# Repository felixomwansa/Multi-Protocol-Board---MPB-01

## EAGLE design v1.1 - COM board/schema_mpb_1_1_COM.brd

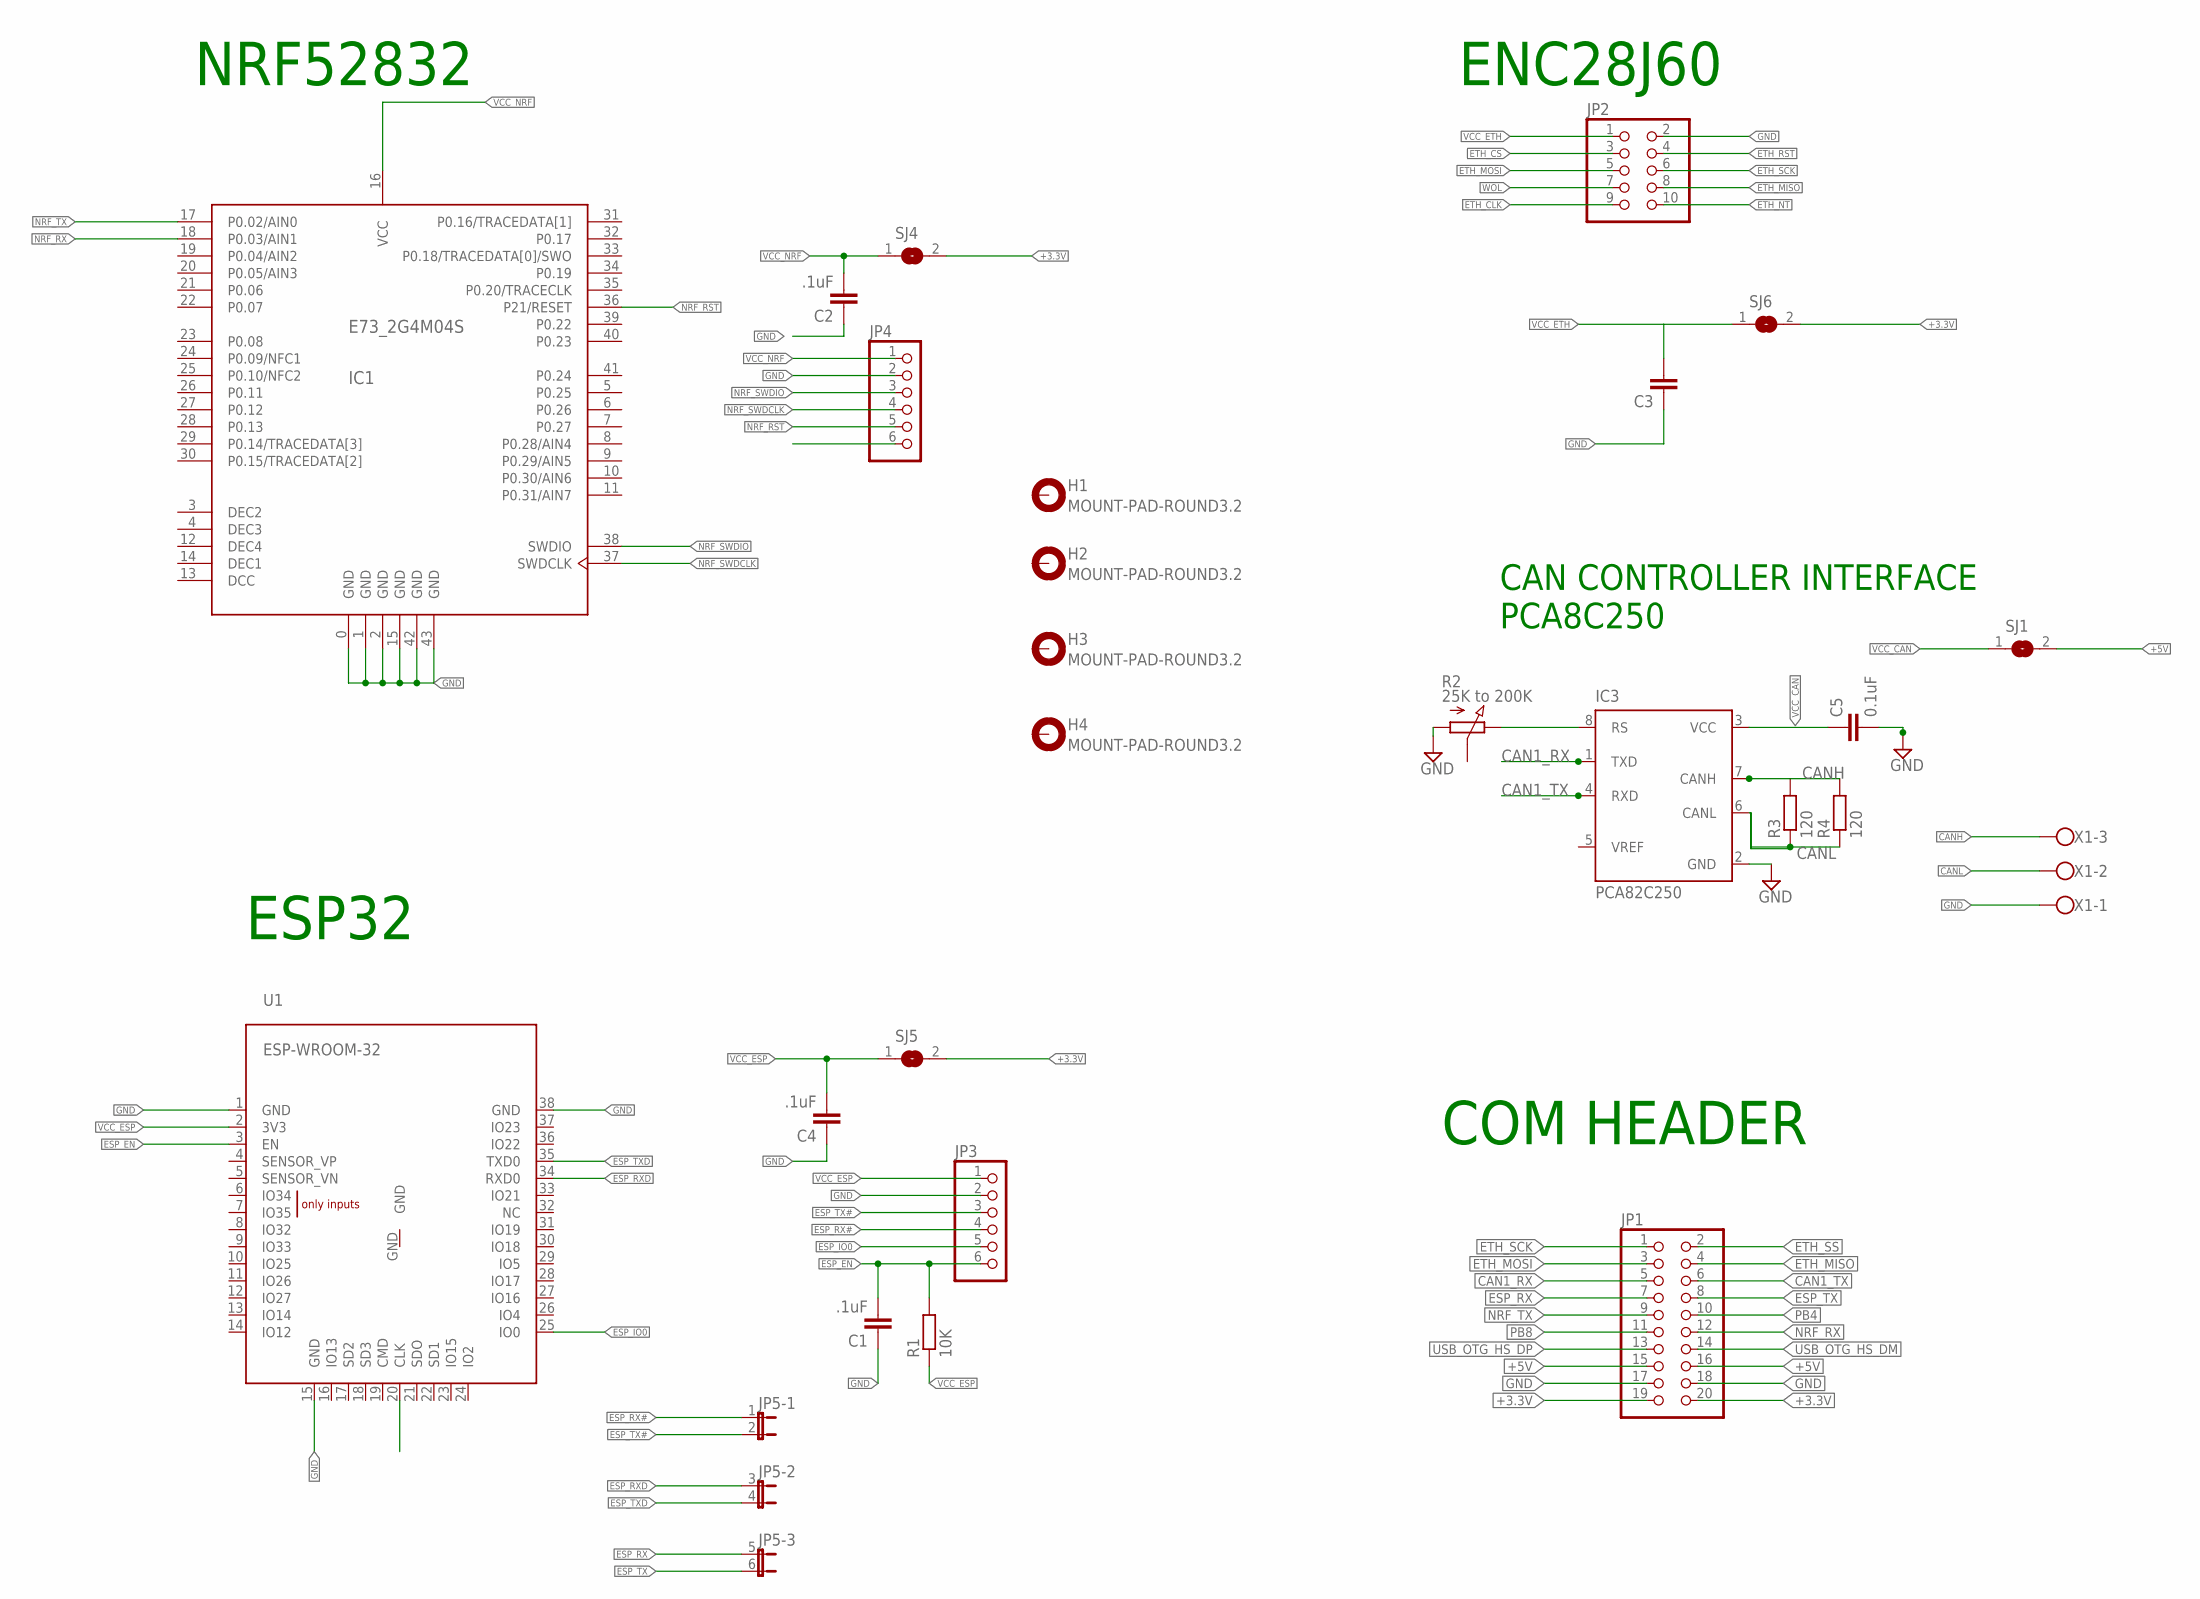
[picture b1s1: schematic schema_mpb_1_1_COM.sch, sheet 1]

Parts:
C1, C2, C4: .1uF; C0603
C3: C-EUC0603; C0603
C5: 0.1uF; C0805
H1, H2, H3, H4: MOUNT-PAD-ROUND3.2; 3,2-PAD
IC1: E73_2G4M04S
IC3: PCA82C250; DIL08
JP1: PINHD-2X10; 2X10
JP2: PINHD-2X5; 2X05
JP3, JP4: PINHD-1X6; 1X06
JP5: JP3QE; JP3Q
R1: 10K; R0603
R2: 25K to 200K; PC25
R3, R4: 120; R0805
SJ1, SJ4, SJ5, SJ6: SJW
U1: ESP-WROOM-32
X1: W237-103

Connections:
+3.3V: JP1.19, JP1.20, SJ4.2, SJ5.2, SJ6.2
+5V: JP1.15, JP1.16, SJ1.2
CAN1_RX: IC3.1 (TXD), JP1.5
CAN1_TX: IC3.4 (RXD), JP1.6
CANH: IC3.7 (CANH), R3.2, R4.2, X1.3
CANL: IC3.6 (CANL), R3.1, R4.1, X1.2
DCC: IC1.13 (DCC)
DEC1: IC1.14 (DEC1)
DEC2: IC1.3 (DEC2)
DEC3: IC1.4 (DEC3)
DEC4: IC1.12 (DEC4)
ESP_EN: C1.2, JP3.6, R1.2, U1.3 (EN)
ESP_IO0: JP3.5, U1.25 (IO0)
ESP_RX: JP1.7, JP5.5 (1)
ESP_RX#: JP3.4, JP5.1
ESP_RXD: JP5.3 (1), U1.34 (RXD0)
ESP_TX: JP1.8, JP5.6 (2)
ESP_TX#: JP3.3, JP5.2
ESP_TXD: JP5.4 (2), U1.35 (TXD0)
ETH_CLK: JP2.9
ETH_CS: JP2.3
ETH_MISO: JP1.4, JP2.8
ETH_MOSI: JP1.3, JP2.5
ETH_NT: JP2.10
ETH_RST: JP2.4
ETH_SCK: JP1.1, JP2.6
ETH_SS: JP1.2
GND: C1.1, C2.1, C3.1, C4.1, C5.2, IC1.0 (GND), IC1.1 (GND), IC1.2 (GND), IC1.15 (GND), IC1.42 (GND), IC1.43 (GND), IC3.2 (GND), JP1.17, JP1.18, JP2.2, JP3.2, JP4.2, R2.A, U1.1 (GND), U1.15 (GND), U1.38 (GND), X1.1
unnamed: IC3.8 (RS), R2.E
NRF_RST: IC1.36 (P21/RESET), JP4.5
NRF_RX: IC1.18 (P0.03/AIN1), JP1.12
NRF_SWDCLK: IC1.37 (SWDCLK), JP4.4
NRF_SWDIO: IC1.38 (SWDIO), JP4.3
NRF_TX: IC1.17 (P0.02/AIN0), JP1.9
PB4: JP1.10
PB8: JP1.11
USB_OTG_HS_DM: JP1.14
USB_OTG_HS_DP: JP1.13
VCC_CAN: C5.1, IC3.3 (VCC), SJ1.1
VCC_ESP: C4.2, JP3.1, R1.1, SJ5.1, U1.2 (3V3)
VCC_ETH: C3.2, JP2.1, SJ6.1
VCC_NRF: C2.2, IC1.16 (VCC), JP4.1, SJ4.1
WOL: JP2.7

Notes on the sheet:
ENC28J60
ESP32
COM HEADER
NRF52832
CAN CONTROLLER INTERFACE PCA8C250

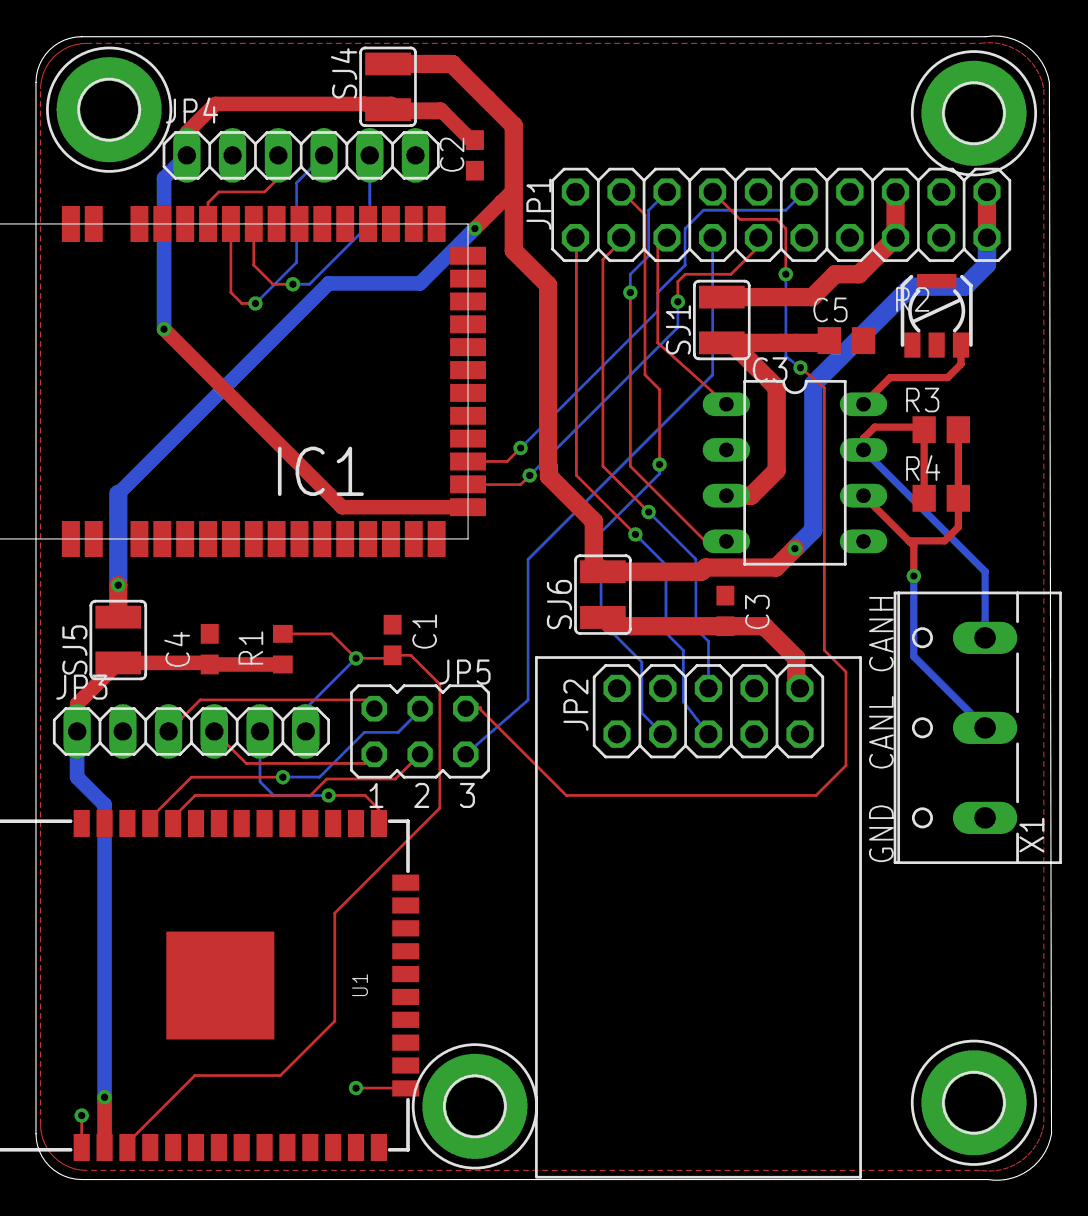
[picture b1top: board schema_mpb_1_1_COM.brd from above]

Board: 2 copper layers, 56.4 x 63.6 mm, 26 parts (0 on the bottom side), 28 nets.

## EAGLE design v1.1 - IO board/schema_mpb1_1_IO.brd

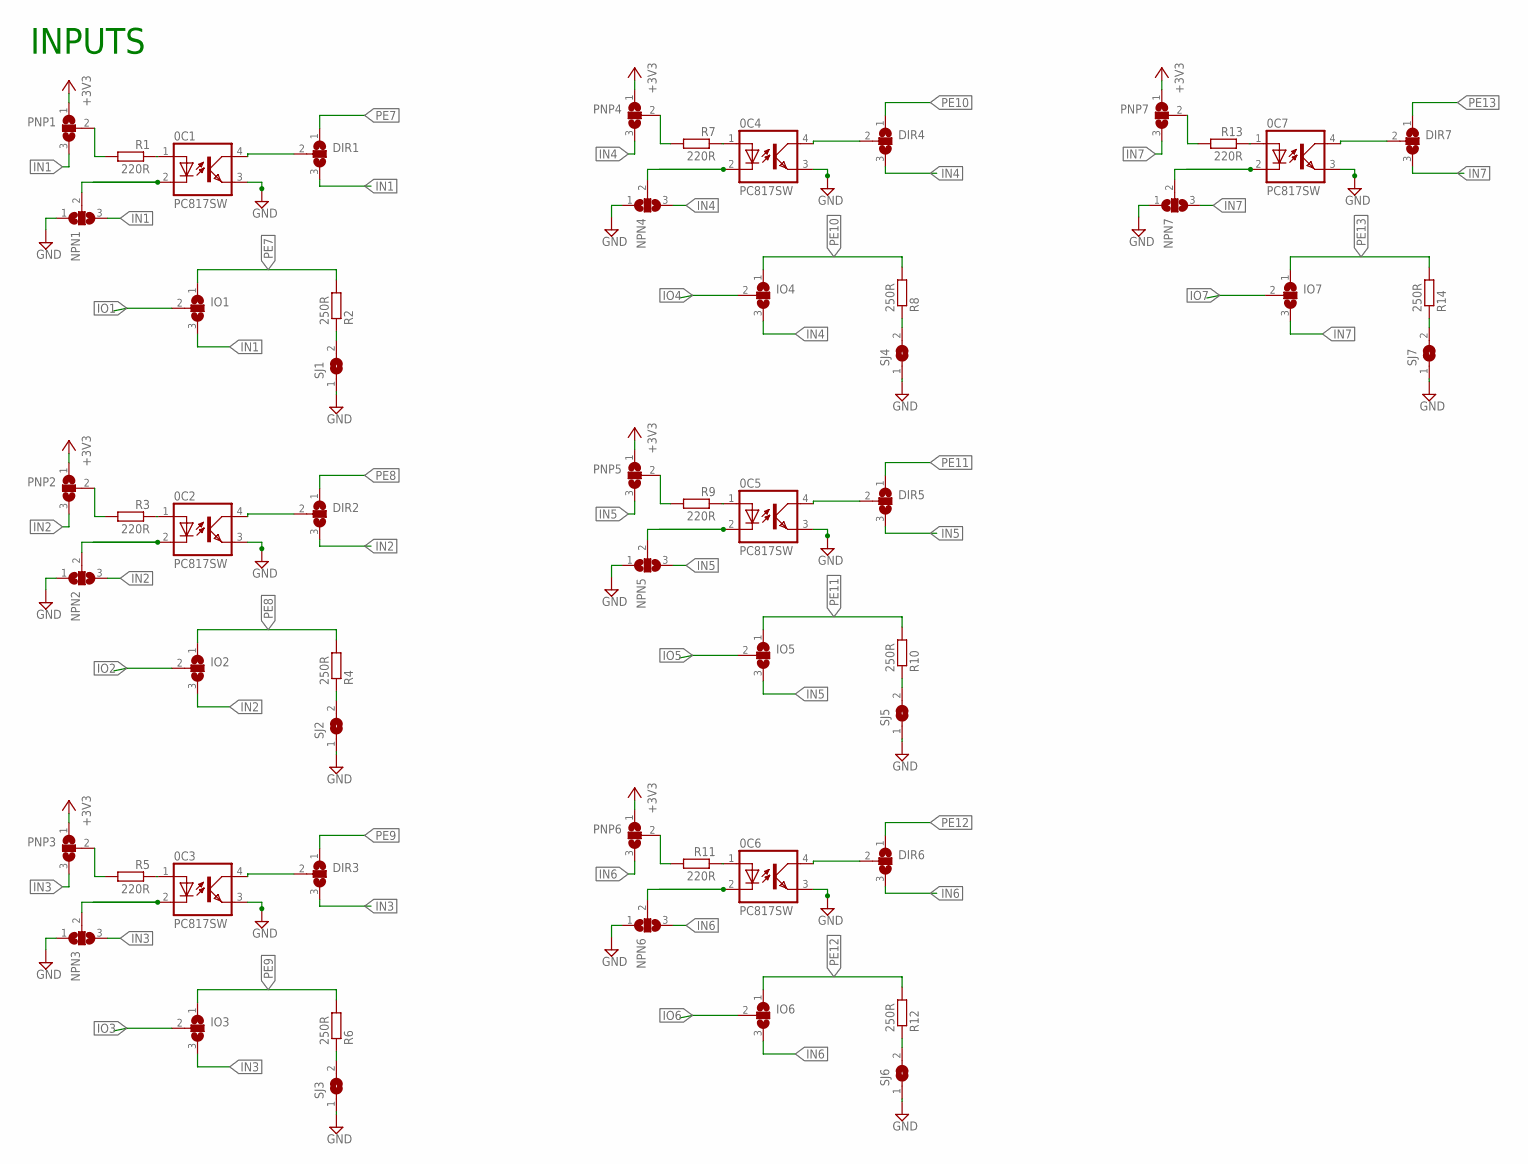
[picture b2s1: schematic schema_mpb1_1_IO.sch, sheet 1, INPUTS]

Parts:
0C1, 0C2, 0C3, 0C4, 0C5, 0C6, 0C7: PC817SW; PC817SMTW
DIR1, DIR2, DIR3, DIR4, DIR5, DIR6, DIR7: SJ2W; SJ_2
IO1, IO2, IO3, IO4, IO5, IO6, IO7: SJ2W; SJ_2
NPN1, NPN2, NPN3, NPN4, NPN5, NPN6, NPN7: SJ2W; SJ_2
PNP1, PNP2, PNP3, PNP4, PNP5, PNP6, PNP7: SJ2W; SJ_2
R1, R3, R5, R7, R9, R11, R13: 220R; R0603
R2, R4, R6, R8, R10, R12, R14: 250R; R0603
SJ1, SJ2, SJ3, SJ4, SJ5, SJ6, SJ7: SJ

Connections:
+3V3: PNP1.1, PNP2.1, PNP3.1, PNP4.1, PNP5.1, PNP6.1, PNP7.1; also elsewhere on the board
GND: 0C1.3 (EMIT), 0C2.3 (EMIT), 0C3.3 (EMIT), 0C4.3 (EMIT), 0C5.3 (EMIT), 0C6.3 (EMIT), 0C7.3 (EMIT), NPN1.1, NPN2.1, NPN3.1, NPN4.1, NPN5.1, NPN6.1, NPN7.1, SJ1.1, SJ2.1, SJ3.1, SJ4.1, SJ5.1, SJ6.1, SJ7.1; also elsewhere on the board
IN1: DIR1.3, IO1.3, NPN1.3, PNP1.3
IN2: DIR2.3, IO2.3, NPN2.3, PNP2.3
IN3: DIR3.3, IO3.3, NPN3.3, PNP3.3
IN4: DIR4.3, IO4.3, NPN4.3, PNP4.3
IN5: DIR5.3, IO5.3, NPN5.3, PNP5.3
IN6: DIR6.3, IO6.3, NPN6.3, PNP6.3
IN7: DIR7.3, IO7.3, NPN7.3, PNP7.3
IO1: IO1.2; also elsewhere on the board
IO2: IO2.2; also elsewhere on the board
IO3: IO3.2; also elsewhere on the board
IO4: IO4.2; also elsewhere on the board
IO5: IO5.2; also elsewhere on the board
IO6: IO6.2; also elsewhere on the board
IO7: IO7.2; also elsewhere on the board
unnamed: PNP1.2, R1.2
unnamed: R2.1, SJ1.2
unnamed: PNP2.2, R3.2
unnamed: 0C2.1 (A), R3.1
unnamed: 0C2.2 (C), NPN2.2
unnamed: 0C2.4 (COL), DIR2.2
unnamed: R4.1, SJ2.2
unnamed: PNP3.2, R5.2
unnamed: 0C3.1 (A), R5.1
unnamed: 0C3.2 (C), NPN3.2
unnamed: 0C3.4 (COL), DIR3.2
unnamed: R6.1, SJ3.2
unnamed: PNP4.2, R7.2
unnamed: 0C4.1 (A), R7.1
unnamed: 0C4.2 (C), NPN4.2
unnamed: 0C4.4 (COL), DIR4.2
unnamed: R8.1, SJ4.2
unnamed: PNP5.2, R9.2
unnamed: 0C5.1 (A), R9.1
unnamed: 0C5.2 (C), NPN5.2
unnamed: 0C5.4 (COL), DIR5.2
unnamed: R10.1, SJ5.2
unnamed: PNP6.2, R11.2
unnamed: 0C6.1 (A), R11.1
unnamed: 0C6.2 (C), NPN6.2
unnamed: 0C6.4 (COL), DIR6.2
unnamed: R12.1, SJ6.2
unnamed: PNP7.2, R13.2
unnamed: 0C7.1 (A), R13.1
unnamed: 0C7.2 (C), NPN7.2
unnamed: 0C1.1 (A), R1.1
unnamed: 0C7.4 (COL), DIR7.2
unnamed: 0C1.2 (C), NPN1.2
unnamed: R14.1, SJ7.2
unnamed: 0C1.4 (COL), DIR1.2
PE7: DIR1.1, IO1.1, R2.2; also elsewhere on the board
PE8: DIR2.1, IO2.1, R4.2; also elsewhere on the board
PE9: DIR3.1, IO3.1, R6.2; also elsewhere on the board
PE10: DIR4.1, IO4.1, R8.2; also elsewhere on the board
PE11: DIR5.1, IO5.1, R10.2; also elsewhere on the board
PE12: DIR6.1, IO6.1, R12.2; also elsewhere on the board
PE13: DIR7.1, IO7.1, R14.2; also elsewhere on the board

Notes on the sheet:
INPUTS

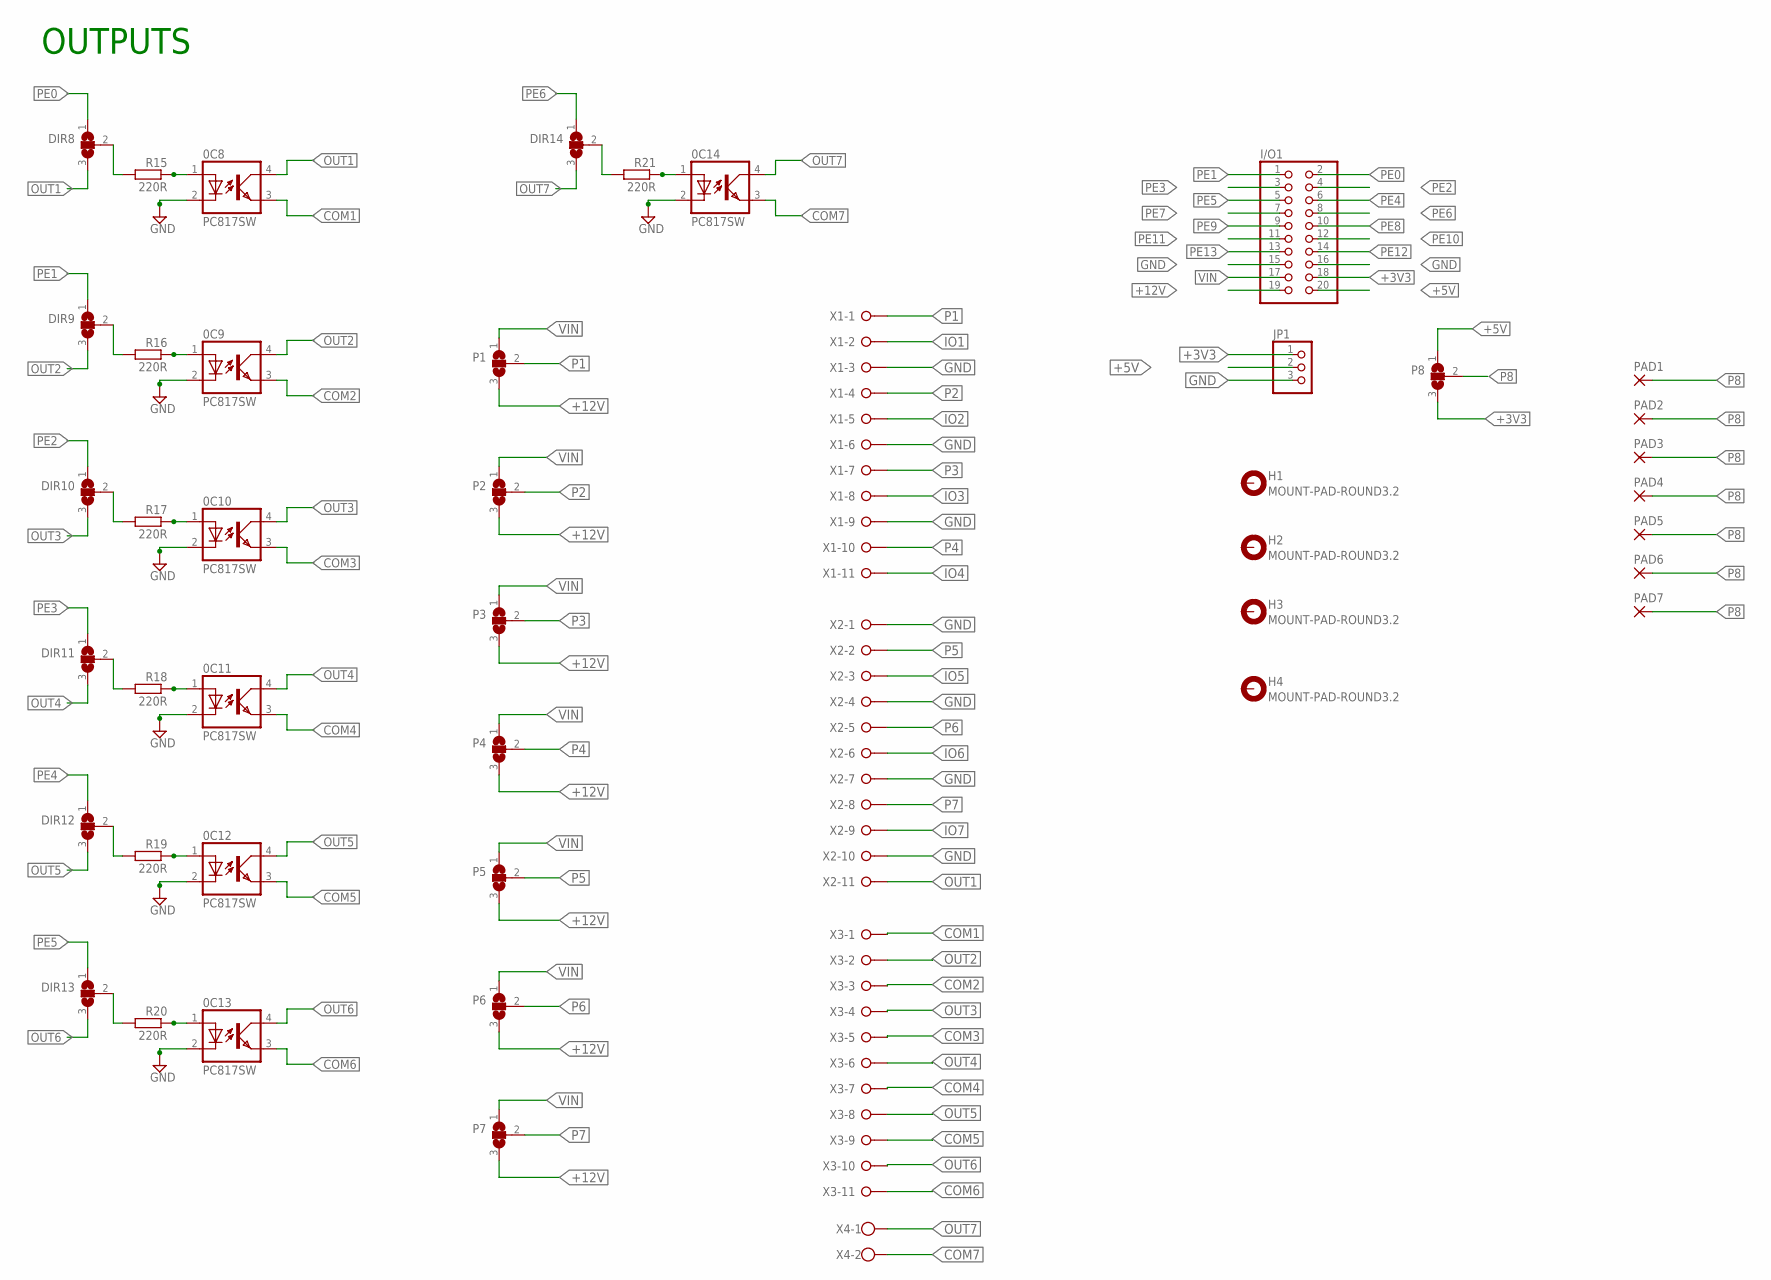
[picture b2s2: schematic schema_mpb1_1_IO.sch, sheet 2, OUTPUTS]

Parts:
0C8, 0C9, 0C10, 0C11, 0C12, 0C13, 0C14: PC817SW; PC817SMTW
DIR8, DIR9, DIR10, DIR11, DIR12, DIR13, DIR14: SJ2W; SJ_2
H1, H2, H3, H4: MOUNT-PAD-ROUND3.2; 3,2-PAD
I/O1: PINHD-2X10_2.54; 2X10
JP1: PINHD-1X3; 1X03
P1, P2, P3, P4, P5, P6, P7, P8: SJ2WW; SJ_2W
PAD1, PAD2, PAD3, PAD4, PAD5, PAD6, PAD7: SMD2; SMD1,27-2,54
R15, R16, R17, R18, R19, R20, R21: 220R; R0603
X1, X2, X3: W237-11P
X4: W237-102

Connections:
+3V3: I/O1.18, JP1.1, P8.3; also elsewhere on the board
+5V: I/O1.20, JP1.2, P8.1
+12V: I/O1.19, P1.3, P2.3, P3.3, P4.3, P5.3, P6.3, P7.3
COM1: 0C8.3 (EMIT), X3.1
COM2: 0C9.3 (EMIT), X3.3
COM3: 0C10.3 (EMIT), X3.5
COM4: 0C11.3 (EMIT), X3.7
COM5: 0C12.3 (EMIT), X3.9
COM6: 0C13.3 (EMIT), X3.11
COM7: 0C14.3 (EMIT), X4.2
GND: 0C8.2 (C), 0C9.2 (C), 0C10.2 (C), 0C11.2 (C), 0C12.2 (C), 0C13.2 (C), 0C14.2 (C), I/O1.15, I/O1.16, JP1.3, X1.3, X1.6, X1.9, X2.1, X2.4, X2.7, X2.10; also elsewhere on the board
IO1: X1.2; also elsewhere on the board
IO2: X1.5; also elsewhere on the board
IO3: X1.8; also elsewhere on the board
IO4: X1.11; also elsewhere on the board
IO5: X2.3; also elsewhere on the board
IO6: X2.6; also elsewhere on the board
IO7: X2.9; also elsewhere on the board
unnamed: DIR14.2, R21.2
unnamed: 0C9.1 (A), R16.1
unnamed: DIR9.2, R16.2
unnamed: 0C10.1 (A), R17.1
unnamed: DIR10.2, R17.2
unnamed: 0C11.1 (A), R18.1
unnamed: DIR11.2, R18.2
unnamed: 0C12.1 (A), R19.1
unnamed: DIR12.2, R19.2
unnamed: 0C13.1 (A), R20.1
unnamed: DIR13.2, R20.2
unnamed: 0C14.1 (A), R21.1
unnamed: DIR8.2, R15.2
unnamed: 0C8.1 (A), R15.1
OUT1: 0C8.4 (COL), DIR8.3, X2.11
OUT2: 0C9.4 (COL), DIR9.3, X3.2
OUT3: 0C10.4 (COL), DIR10.3, X3.4
OUT4: 0C11.4 (COL), DIR11.3, X3.6
OUT5: 0C12.4 (COL), DIR12.3, X3.8
OUT6: 0C13.4 (COL), DIR13.3, X3.10
OUT7: 0C14.4 (COL), DIR14.3, X4.1
P1: P1.2, X1.1
P2: P2.2, X1.4
P3: P3.2, X1.7
P4: P4.2, X1.10
P5: P5.2, X2.2
P6: P6.2, X2.5
P7: P7.2, X2.8
P8: P8.2, PAD1.1, PAD2.1, PAD3.1, PAD4.1, PAD5.1, PAD6.1, PAD7.1
PE0: DIR8.1, I/O1.2
PE1: DIR9.1, I/O1.1
PE2: DIR10.1, I/O1.4
PE3: DIR11.1, I/O1.3
PE4: DIR12.1, I/O1.6
PE5: DIR13.1, I/O1.5
PE6: DIR14.1, I/O1.8
PE7: I/O1.7; also elsewhere on the board
PE8: I/O1.10; also elsewhere on the board
PE9: I/O1.9; also elsewhere on the board
PE10: I/O1.12; also elsewhere on the board
PE11: I/O1.11; also elsewhere on the board
PE12: I/O1.14; also elsewhere on the board
PE13: I/O1.13; also elsewhere on the board
VIN: I/O1.17, P1.1, P2.1, P3.1, P4.1, P5.1, P6.1, P7.1

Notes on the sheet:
OUTPUTS

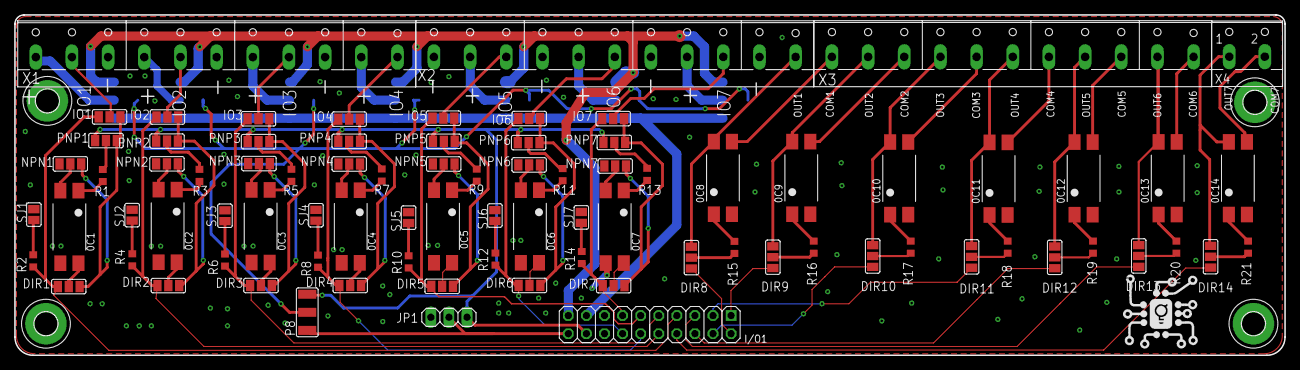
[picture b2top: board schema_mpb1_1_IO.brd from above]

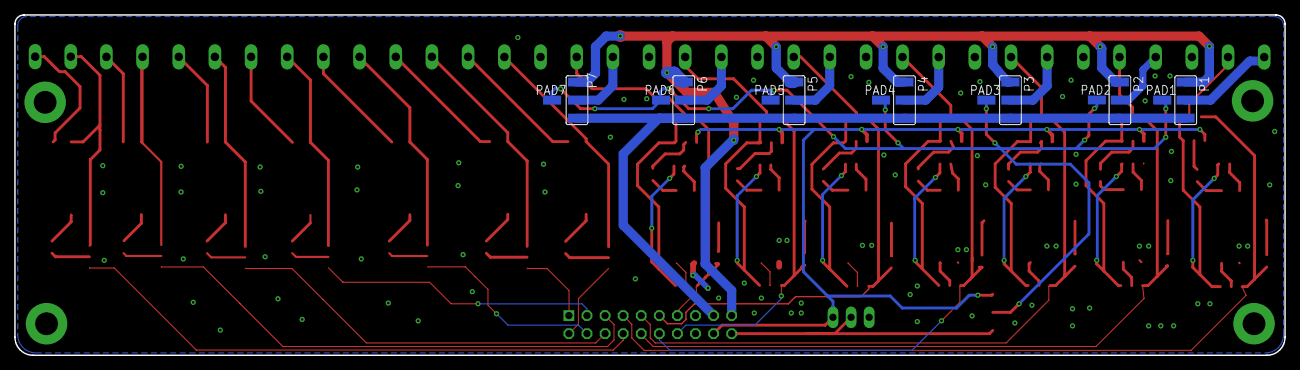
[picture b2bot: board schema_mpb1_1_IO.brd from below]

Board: 2 copper layers, 178.4 x 47.8 mm, 102 parts (14 on the bottom side), 104 nets.

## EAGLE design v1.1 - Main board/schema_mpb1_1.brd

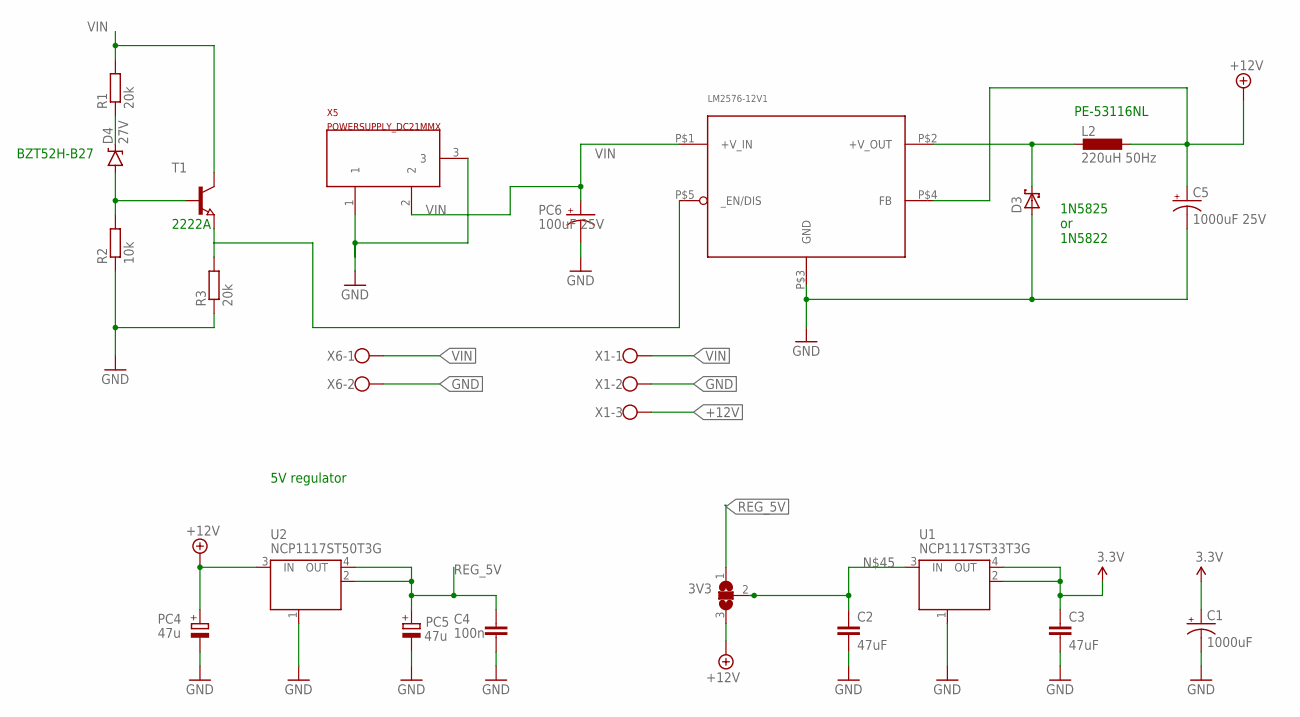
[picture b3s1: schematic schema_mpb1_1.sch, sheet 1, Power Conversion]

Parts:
3V3: SJ2W; SJ_2
C1: 1000uF; E5-6
C2, C3: 47uF; C0603
C4: 100n; C0603-ROUND
C5: 1000uF 25V; E5-6
D3: 1N5908; C4111-15
D4: 27V; SOD-123
L2: 220uH 50Hz; KM-4.0
LM2576-12V1: LM2576-T05D; TO220-5_STAGGERED
PC4, PC5: 47u; PANASONIC_D
PC6: 100uF 25V; E5-6
R1, R3: 20k; R0603
R2: 10k; R0603
T1: NPN-TRANSISTOR_SOT23; SOT23
U1: NCP1117ST33T3G; SOT223
U2: NCP1117ST50T3G; SOT223
X1: W237-103
X5: POWERSUPPLY_DC21MMX; POWERSUPPLY_DC-21MM
X6: W237-102

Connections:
3.3V: C1.+, C3.1, U1.2 (OUT), U1.4 (OUT); also elsewhere on the board
+12V: 3V3.3, C5.+, L2.P$2 (2), LM2576-12V1.P$4 (FB), PC4.+, U2.3 (IN), X1.3; also elsewhere on the board
GND: C1.-, C2.2, C3.2, C4.1, C5.-, D3.A, LM2576-12V1.P$3 (GND), PC4.-, PC5.-, PC6.-, R2.1, R3.1, U1.1 (GND/ADJ), U2.1 (GND/ADJ), X1.2, X5.1, X5.3, X6.2; also elsewhere on the board
unnamed: D3.C, L2.P$1 (1), LM2576-12V1.P$2 (+V_OUT)
unnamed: D4.A, R2.2, T1.1 (B)
unnamed: D4.C, R1.1
unnamed: LM2576-12V1.P$5 (_EN/DIS), R3.2, T1.2 (E)
unnamed: 3V3.2, C2.1, U1.3 (IN)
REG_5V: 3V3.1, C4.2, PC5.+, U2.2 (OUT), U2.4 (OUT); also elsewhere on the board
VIN: LM2576-12V1.P$1 (+V_IN), PC6.+, R1.2, T1.3 (C), X1.1, X5.2, X6.1; also elsewhere on the board

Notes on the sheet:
5V regulator
1N5825 or 1N5822
PE-53116NL
BZT52H-B27
2222A

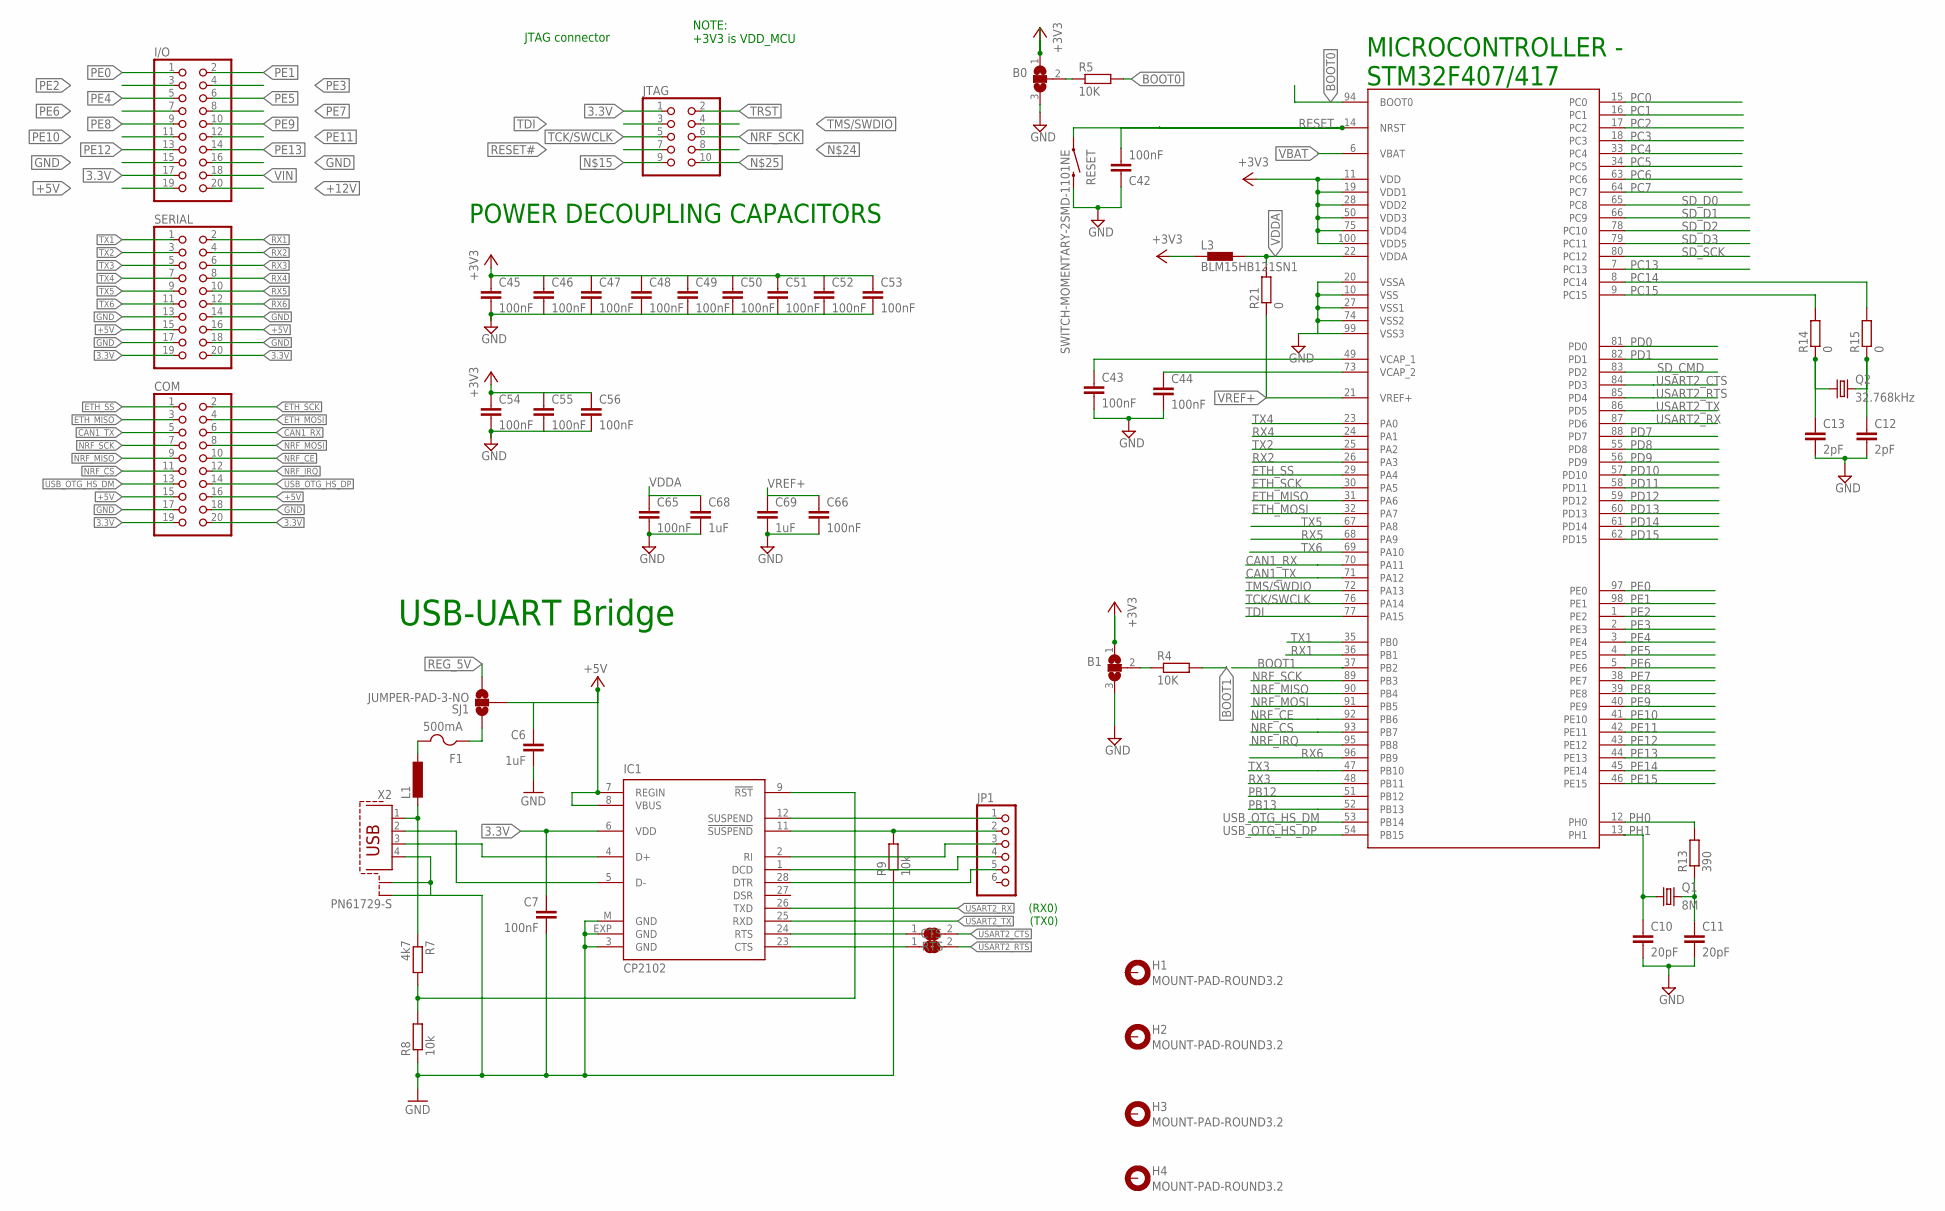
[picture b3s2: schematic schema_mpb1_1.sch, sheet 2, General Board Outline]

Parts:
B0, B1: SJ2W; SJ_2
C6: 1uF; C0603-ROUND
C7: 100nF; C0603-ROUND
C10, C11: 20pF; C0603
C12, C13: 2pF; C0603
C42, C43, C44, C45, C46, C47, C48, C49, C50, C51, C52, C53, C54, C55, C56, C65, C66: 100nF; C0603
C68, C69: 1uF; C0603
COM: PINHD-2X10_2.54; 2X10
CTS: SJ
F1: 500mA; 1812
H1, H2, H3, H4: MOUNT-PAD-ROUND3.2; 3,2-PAD
I/O: PINHD-2X10_2.54; 2X10
IC1: CP2102; MLP28
JP1: PINHD-1X6; 1X06
JTAG: PINHD-2X05_2.00; 2X05M
L1: L-EUL1812; L1812
L3: BLM15HB121SN1; 0402
Q1: 8M; HC49UP
Q2: 32.768kHz; HC49UP
R4, R5: 10K; R0603
R7: 4k7; R0603
R8, R9: 10k; R0603
R13: 390; R0603
R14, R15, R21: 0; R0603
RESET: SWITCH-MOMENTARY-2SMD-1101NE; TACTILE-SWITCH-1101NE
RTS: SJ
SERIAL: PINHD-2X10_2.54; 2X10
SJ1: JUMPER-PAD-3-NO; PAD-JUMPER-3-NO_YES_SILK_FULL_BOX_WIDE_SPACING
U$2: STM32F40XSTM32D40X; LQFP100
X2: PN61729-S

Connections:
3.3V: B0.1, B1.1, C7.1, C45.1, C46.1, C47.1, C48.1, C49.1, C50.1, C51.1, C52.1, C53.1, C54.1, C55.1, C56.1, COM.19, COM.20, I/O.17, IC1.6 (VDD), JTAG.1, L3.1, SERIAL.19, SERIAL.20, U$2.11 (VDD), U$2.19 (VDD1), U$2.28 (VDD2), U$2.50 (VDD3), U$2.75 (VDD4), U$2.100 (VDD5); also elsewhere on the board
+5V: C6.1, COM.15, COM.16, I/O.19, IC1.7 (REGIN), IC1.8 (VBUS), SERIAL.15, SERIAL.16, SJ1.2
+12V: I/O.20; also elsewhere on the board
BOOT0: R5.2, U$2.94 (BOOT0)
BOOT1: R4.2, U$2.37 (PB2)
CAN1_RX: COM.6, U$2.70 (PA11)
CAN1_TX: COM.5, U$2.71 (PA12)
ESP_RX: COM.8, U$2.91 (PB5)
ESP_TX: COM.7, JTAG.6, U$2.89 (PB3)
ETH_MISO: COM.3, U$2.31 (PA6)
ETH_MOSI: COM.4, U$2.32 (PA7)
ETH_SCK: COM.2, U$2.30 (PA5)
ETH_SS: COM.1, U$2.29 (PA4)
GND: B0.3, B1.3, C6.2, C7.2, C10.2, C11.2, C12.2, C13.2, C42.1, C43.2, C44.2, C45.2, C46.2, C47.2, C48.2, C49.2, C50.2, C51.2, C52.2, C53.2, C54.2, C55.2, C56.2, C65.2, C66.2, C68.2, C69.2, COM.17, COM.18, I/O.15, I/O.16, IC1.3 (GND), IC1.EXP (GND), IC1.M (GND), R8.1, R9.1, RESET.2, SERIAL.13, SERIAL.14, SERIAL.17, SERIAL.18, U$2.10 (VSS), U$2.20 (VSSA), U$2.27 (VSS1), U$2.74 (VSS2), U$2.99 (VSS3), X2.4, X2.S1, X2.S2; also elsewhere on the board
unnamed: B1.2, R4.1
unnamed: B0.2, R5.1
unnamed: IC1.9 (!RST), R7.2, R8.2
unnamed: C11.1, Q1.2, R13.1
unnamed: C12.1, Q2.2, R15.1
unnamed: IC1.2 (RI), JP1.3
unnamed: C13.1, Q2.1, R14.1
unnamed: IC1.5 (D-), X2.2
unnamed: IC1.4 (D+), X2.3
unnamed: C44.1, U$2.73 (VCAP_2)
unnamed: L1.2, R7.1, X2.1
unnamed: F1.2, L1.1
unnamed: IC1.1 (DCD), JP1.4
unnamed: C43.1, U$2.49 (VCAP_1)
unnamed: IC1.11 (!SUSPEND), JP1.2, R9.2
unnamed: IC1.12 (SUSPEND), JP1.1
unnamed: IC1.28 (DTR), JP1.5
unnamed: CTS.1, IC1.24 (RTS)
unnamed: IC1.23 (CTS), RTS.1
NRF_RX: COM.11, U$2.93 (PB7)
NRF_TX: COM.10, U$2.92 (PB6)
PB4: COM.9, U$2.90 (PB4)
PB8: COM.12, U$2.95 (PB8)
PB12: U$2.51 (PB12)
PB13: U$2.52 (PB13)
PC0: U$2.15 (PC0)
PC1: U$2.16 (PC1)
PC2: U$2.17 (PC2)
PC3: U$2.18 (PC3)
PC4: U$2.33 (PC4)
PC5: U$2.34 (PC5)
PC6: U$2.63 (PC6)
PC7: U$2.64 (PC7)
PC13: U$2.7 (PC13)
PC14: R15.2, U$2.8 (PC14)
PC15: R14.2, U$2.9 (PC15)
PD0: U$2.81 (PD0)
PD1: U$2.82 (PD1)
PD7: U$2.88 (PD7)
PD8: U$2.55 (PD8)
PD9: U$2.56 (PD9)
PD10: U$2.57 (PD10)
PD11: U$2.58 (PD11)
PD12: U$2.59 (PD12)
PD13: U$2.60 (PD13)
PD14: U$2.61 (PD14)
PD15: U$2.62 (PD15)
PE0: I/O.1, U$2.97 (PE0)
PE1: I/O.2, U$2.98 (PE1)
PE2: I/O.3, U$2.1 (PE2)
PE3: I/O.4, U$2.2 (PE3)
PE4: I/O.5, U$2.3 (PE4)
PE5: I/O.6, U$2.4 (PE5)
PE6: I/O.7, U$2.5 (PE6)
PE7: I/O.8, U$2.38 (PE7)
PE8: I/O.9, U$2.39 (PE8)
PE9: I/O.10, U$2.40 (PE9)
PE10: I/O.11, U$2.41 (PE10)
PE11: I/O.12, U$2.42 (PE11)
PE12: I/O.13, U$2.43 (PE12)
PE13: I/O.14, U$2.44 (PE13)
PE14: U$2.45 (PE14)
PE15: U$2.46 (PE15)
PH0: R13.2, U$2.12 (PH0)
PH1: C10.1, Q1.1, U$2.13 (PH1)
REG_5V: SJ1.3; also elsewhere on the board
RESET: C42.2, RESET.1, U$2.14 (NRST)
RESET#: JTAG.7
RX1: SERIAL.2, U$2.36 (PB1)
RX2: SERIAL.4, U$2.26 (PA3)
RX3: SERIAL.6, U$2.48 (PB11)
RX4: SERIAL.8, U$2.24 (PA1)
RX5: SERIAL.10, U$2.68 (PA9)
RX6: SERIAL.12, U$2.96 (PB9)
SD_CMD: U$2.83 (PD2)
SD_D0: U$2.65 (PC8)
SD_D1: U$2.66 (PC9)
SD_D2: U$2.78 (PC10)
SD_D3: U$2.79 (PC11)
SD_SCK: U$2.80 (PC12)
TCK/SWCLK: JTAG.5, U$2.76 (PA14)
TDI: JTAG.3, U$2.77 (PA15)
TMS/SWDIO: JTAG.4, U$2.72 (PA13)
TRST: JTAG.2
TX1: SERIAL.1, U$2.35 (PB0)
TX2: SERIAL.3, U$2.25 (PA2)
TX3: SERIAL.5, U$2.47 (PB10)
TX4: SERIAL.7, U$2.23 (PA0)
TX5: SERIAL.9, U$2.67 (PA8)
TX6: SERIAL.11, U$2.69 (PA10)
USART2_CTS: CTS.2, U$2.84 (PD3)
USART2_RTS: RTS.2, U$2.85 (PD4)
USART2_RX: IC1.26 (TXD), U$2.87 (PD6)
USART2_TX: IC1.25 (RXD), U$2.86 (PD5)
USB_OTG_HS_DM: COM.13, U$2.53 (PB14)
USB_OTG_HS_DP: COM.14, U$2.54 (PB15)
VBAT: U$2.6 (VBAT)
VDDA: C65.1, C68.1, L3.2, R21.2, U$2.22 (VDDA)
VIN: I/O.18; also elsewhere on the board
VREF+: C66.1, C69.1, R21.1, U$2.21 (VREF+)
VUSB2: F1.1, SJ1.1

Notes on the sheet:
JTAG connector
NOTE: +3V3 is VDD_MCU
MICROCONTROLLER - STM32F407/417
POWER DECOUPLING CAPACITORS
USB-UART Bridge
(RX0)
(TX0)

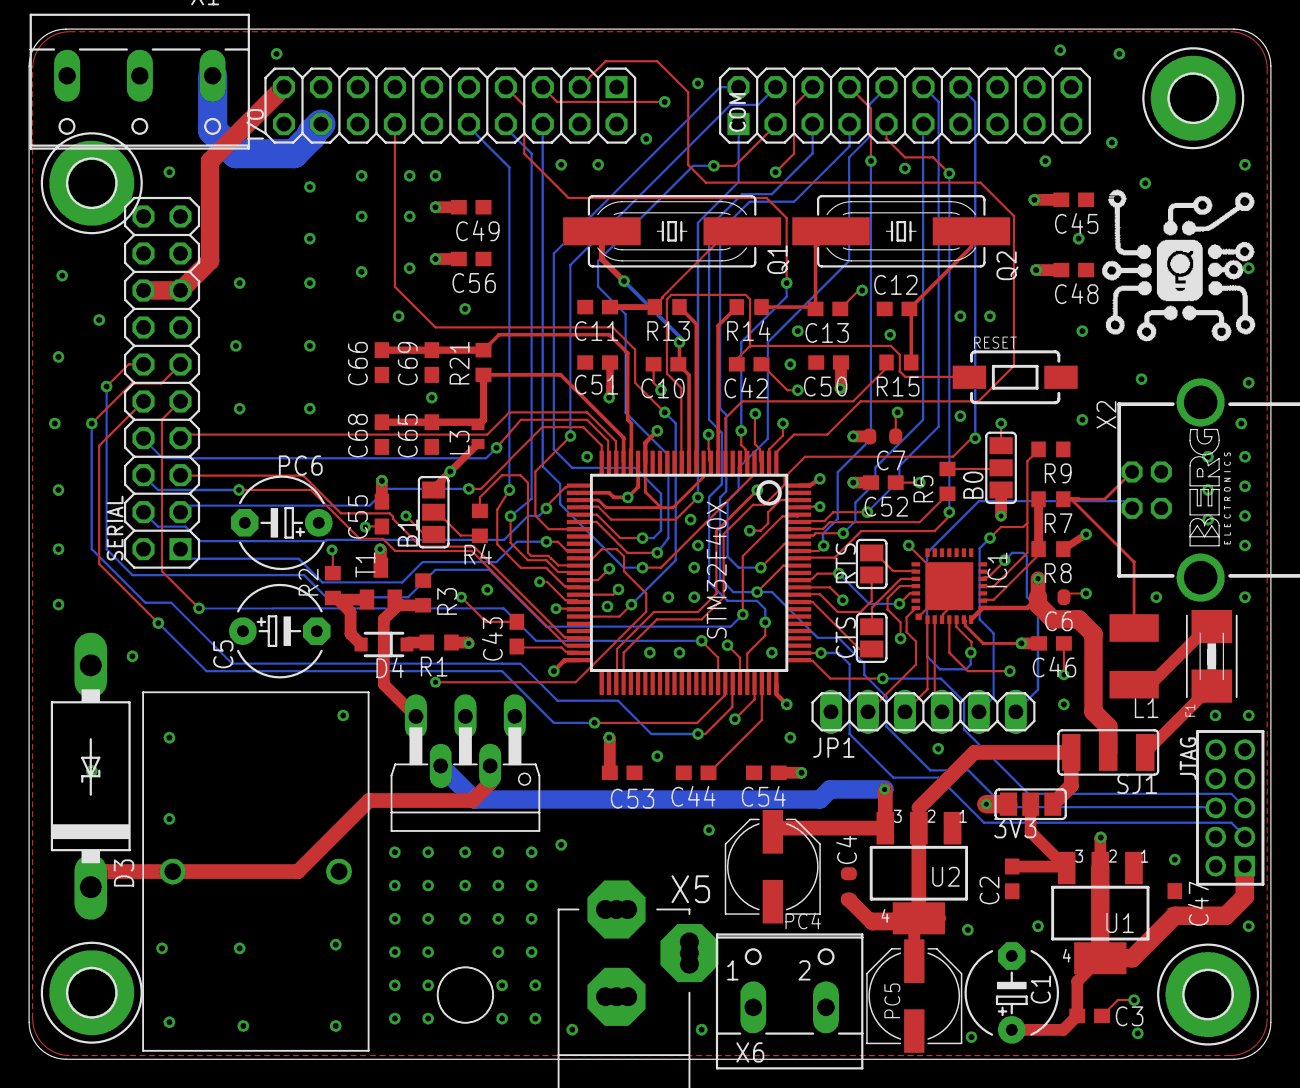
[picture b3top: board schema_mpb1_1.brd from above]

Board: 4 copper layers, 85.3 x 70.8 mm, 79 parts (0 on the bottom side), 87 nets.

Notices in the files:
parts and their libraries:
esp32: Creative Commons Attribution-ShareAlike 4.0 International
SparkFun-Electromechanical: Licensing: Creative Commons ShareAlike 4.0 International - https://creativecommons.org/licenses/by-sa/4.0
